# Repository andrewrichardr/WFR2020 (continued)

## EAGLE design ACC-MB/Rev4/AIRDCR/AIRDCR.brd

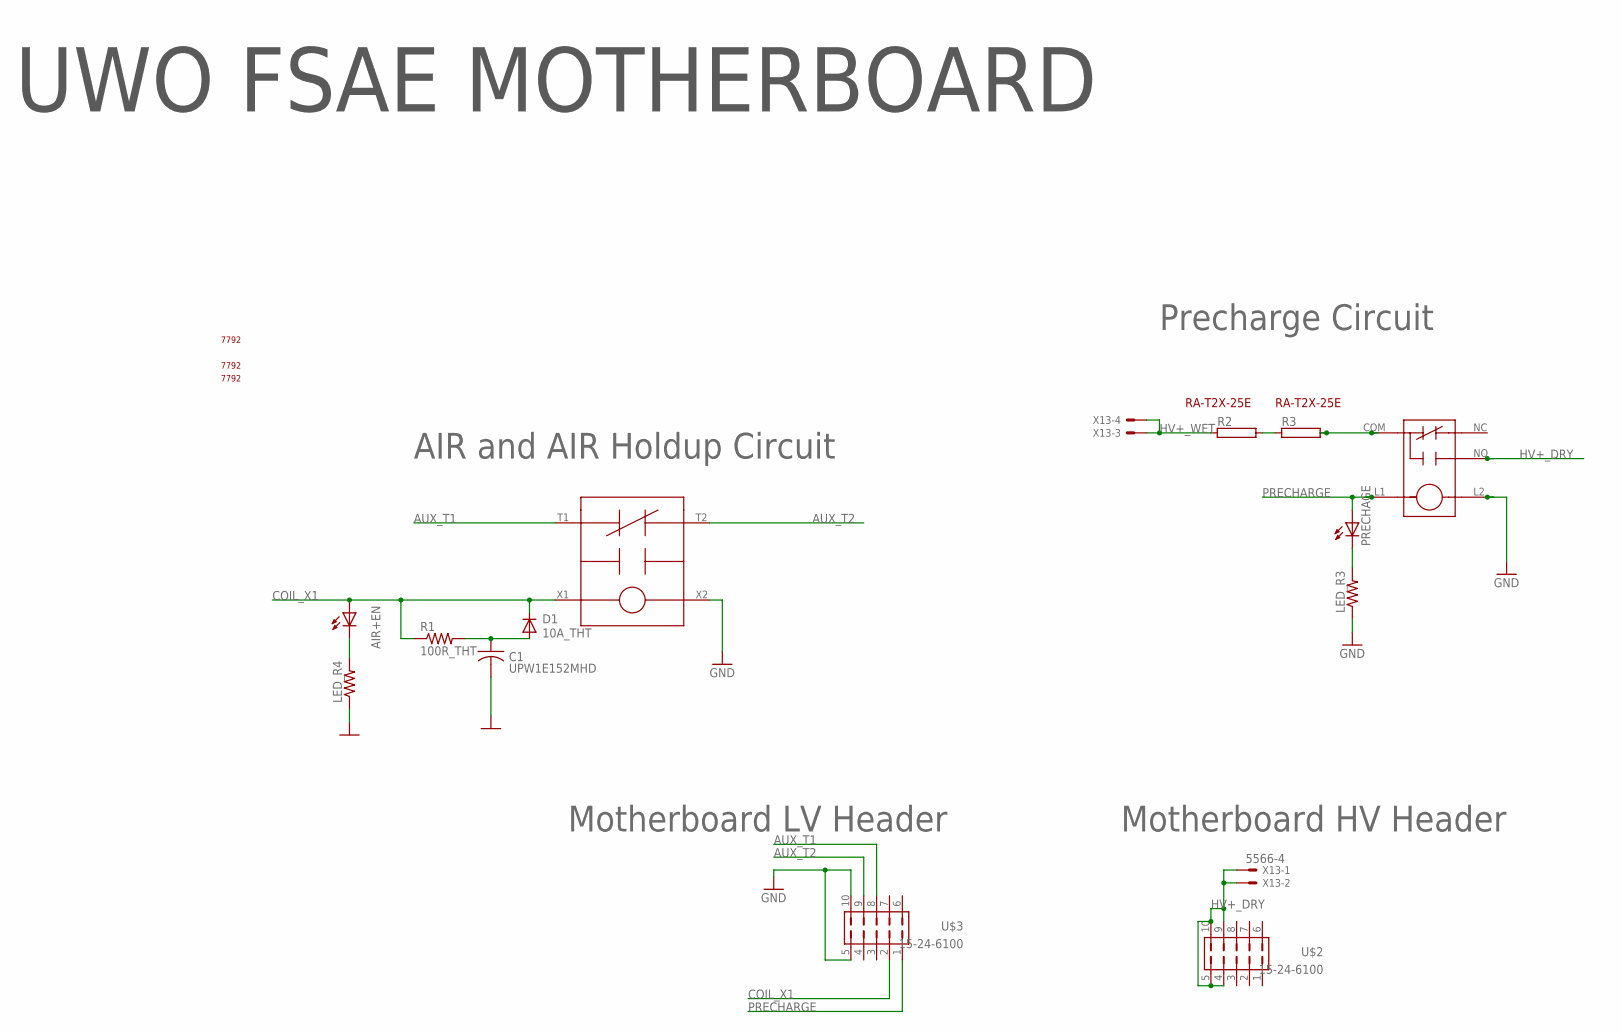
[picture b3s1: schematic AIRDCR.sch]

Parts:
AIR+EN: LEDCHIPLED_0805; CHIPLED_0805
C1: UPW1E152MHD; CAPPRD750W65D1800H3700B
D1: 10A_THT; DIOAD1570W120L850D500B
LED_R3, LED_R4: R-US_R0805; R0805
PRECHAGE: LEDCHIPLED_0805; CHIPLED_0805
R1: 100R_THT; RESAD976W63L650D250B
R2, R3: RMG100-V; TO-247-2V
U$1: GV245BPB; GV224
U$2, U$3: 15-24-6100
U$4: G81C335
U$5, U$6, U$7: 7792
U$8, U$9: RA-T2X-25E
X13: 5566-4

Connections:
AUX_T1: U$1.T1, U$3.8
AUX_T2: U$1.T2, U$3.9
COIL_X1: AIR+EN.A, D1.1 (C), R1.1, U$1.X1, U$3.2
GND: C1.2, LED_R3.1, LED_R4.1, U$1.X2, U$3.5, U$3.10, U$4.L2
HV+_DRY: U$2.4, U$2.5, U$2.9, U$2.10, U$4.NO, X13.1, X13.2
HV+_WET: R2.1, X13.3, X13.4
unnamed: LED_R3.2, PRECHAGE.C
unnamed: C1.1, D1.2 (A), R1.2
unnamed: R2.2, R3.1
unnamed: AIR+EN.C, LED_R4.2
unnamed: R3.2, U$4.COM
PRECHARGE: PRECHAGE.A, U$3.1, U$4.L1

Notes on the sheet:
UWO FSAE MOTHERBOARD
AIR and AIR Holdup Circuit
Precharge Circuit
Motherboard LV Header
Motherboard HV Header

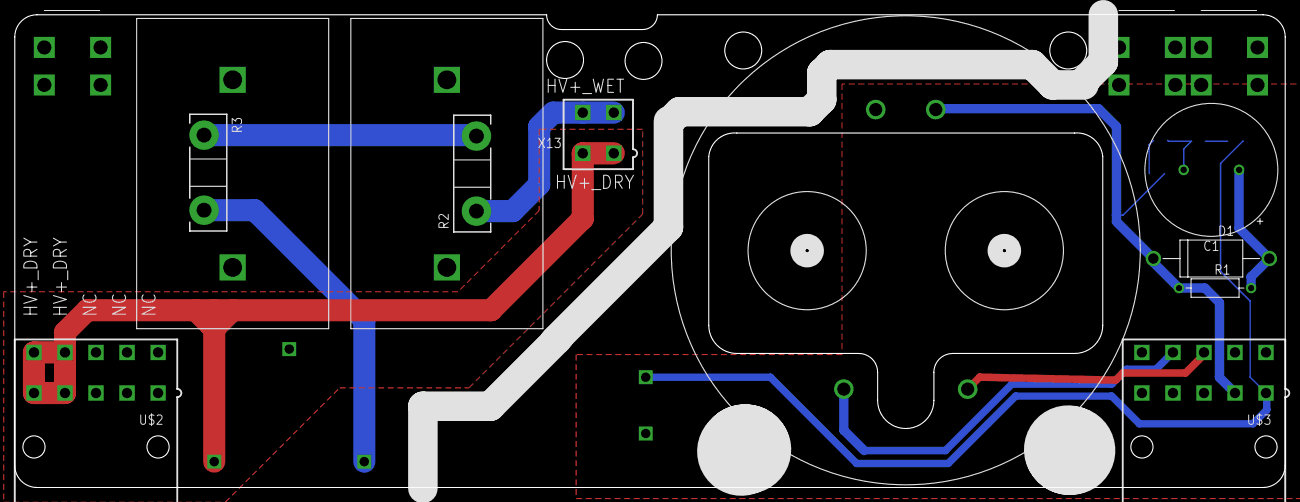
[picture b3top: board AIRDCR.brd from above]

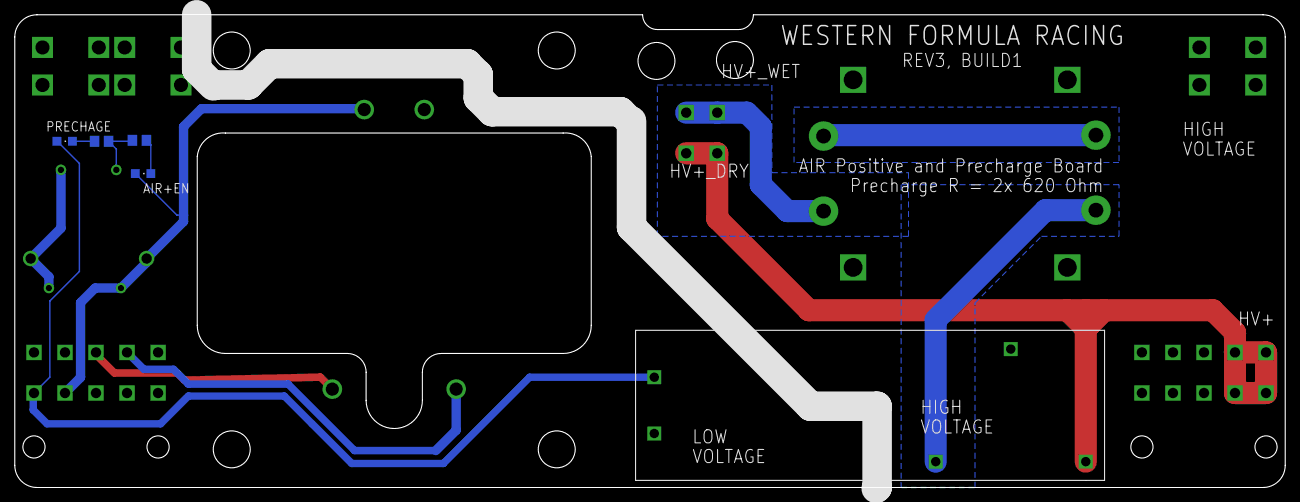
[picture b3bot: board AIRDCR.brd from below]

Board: 2 copper layers, 172.0 x 64.0 mm, 19 parts (5 on the bottom side), 12 nets.

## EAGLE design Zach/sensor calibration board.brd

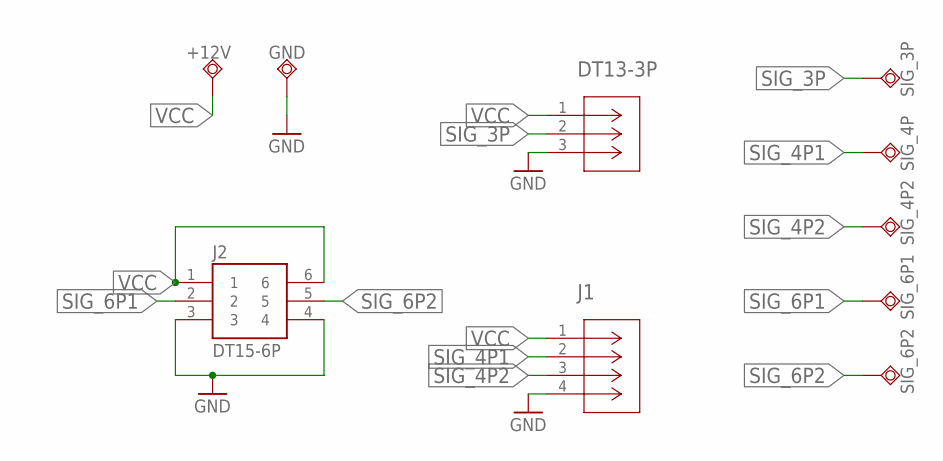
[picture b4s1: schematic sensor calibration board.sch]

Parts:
+12V: TPSQPAD1-20Y; P1-20Y
DT13-3P: DTF13-3P; CONN3_DTF13-3P
GND: TPSQPAD1-20Y; P1-20Y
J1: DT15-4P-G003S; CONN4_DT15-4P-G003
J2: DT15-6P; TE_DT15-6P
SIG_3P, SIG_4P, SIG_4P2, SIG_6P1, SIG_6P2: TPSQPAD1-20Y; P1-20Y

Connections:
GND: DT13-3P.3, GND.1, J1.4, J2.3, J2.4
SIG_3P: DT13-3P.2, SIG_3P.1
SIG_4P1: J1.2, SIG_4P.1
SIG_4P2: J1.3, SIG_4P2.1
SIG_6P1: J2.2, SIG_6P1.1
SIG_6P2: J2.5, SIG_6P2.1
VCC: +12V.1, DT13-3P.1, J1.1, J2.1, J2.6

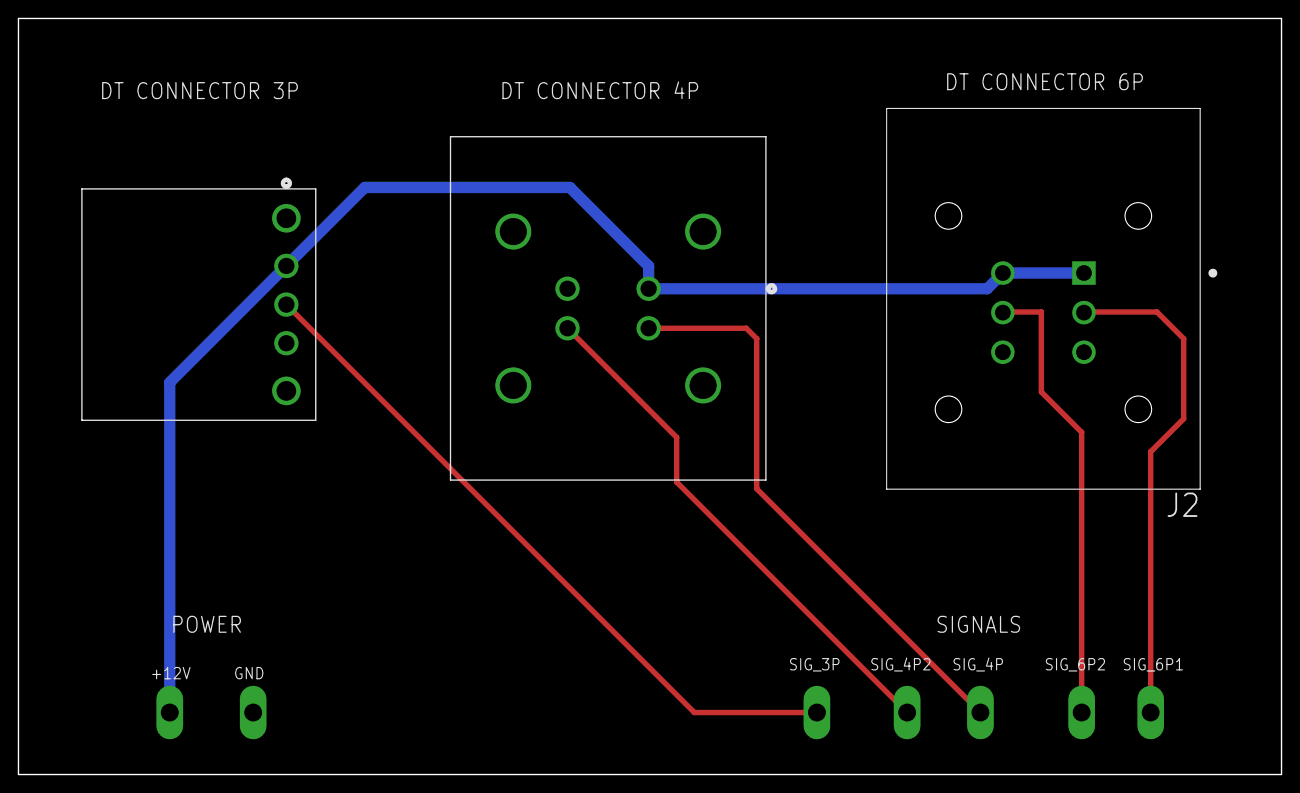
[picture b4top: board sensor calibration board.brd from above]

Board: 2 copper layers, 142.0 x 85.0 mm, 10 parts (0 on the bottom side), 7 nets.

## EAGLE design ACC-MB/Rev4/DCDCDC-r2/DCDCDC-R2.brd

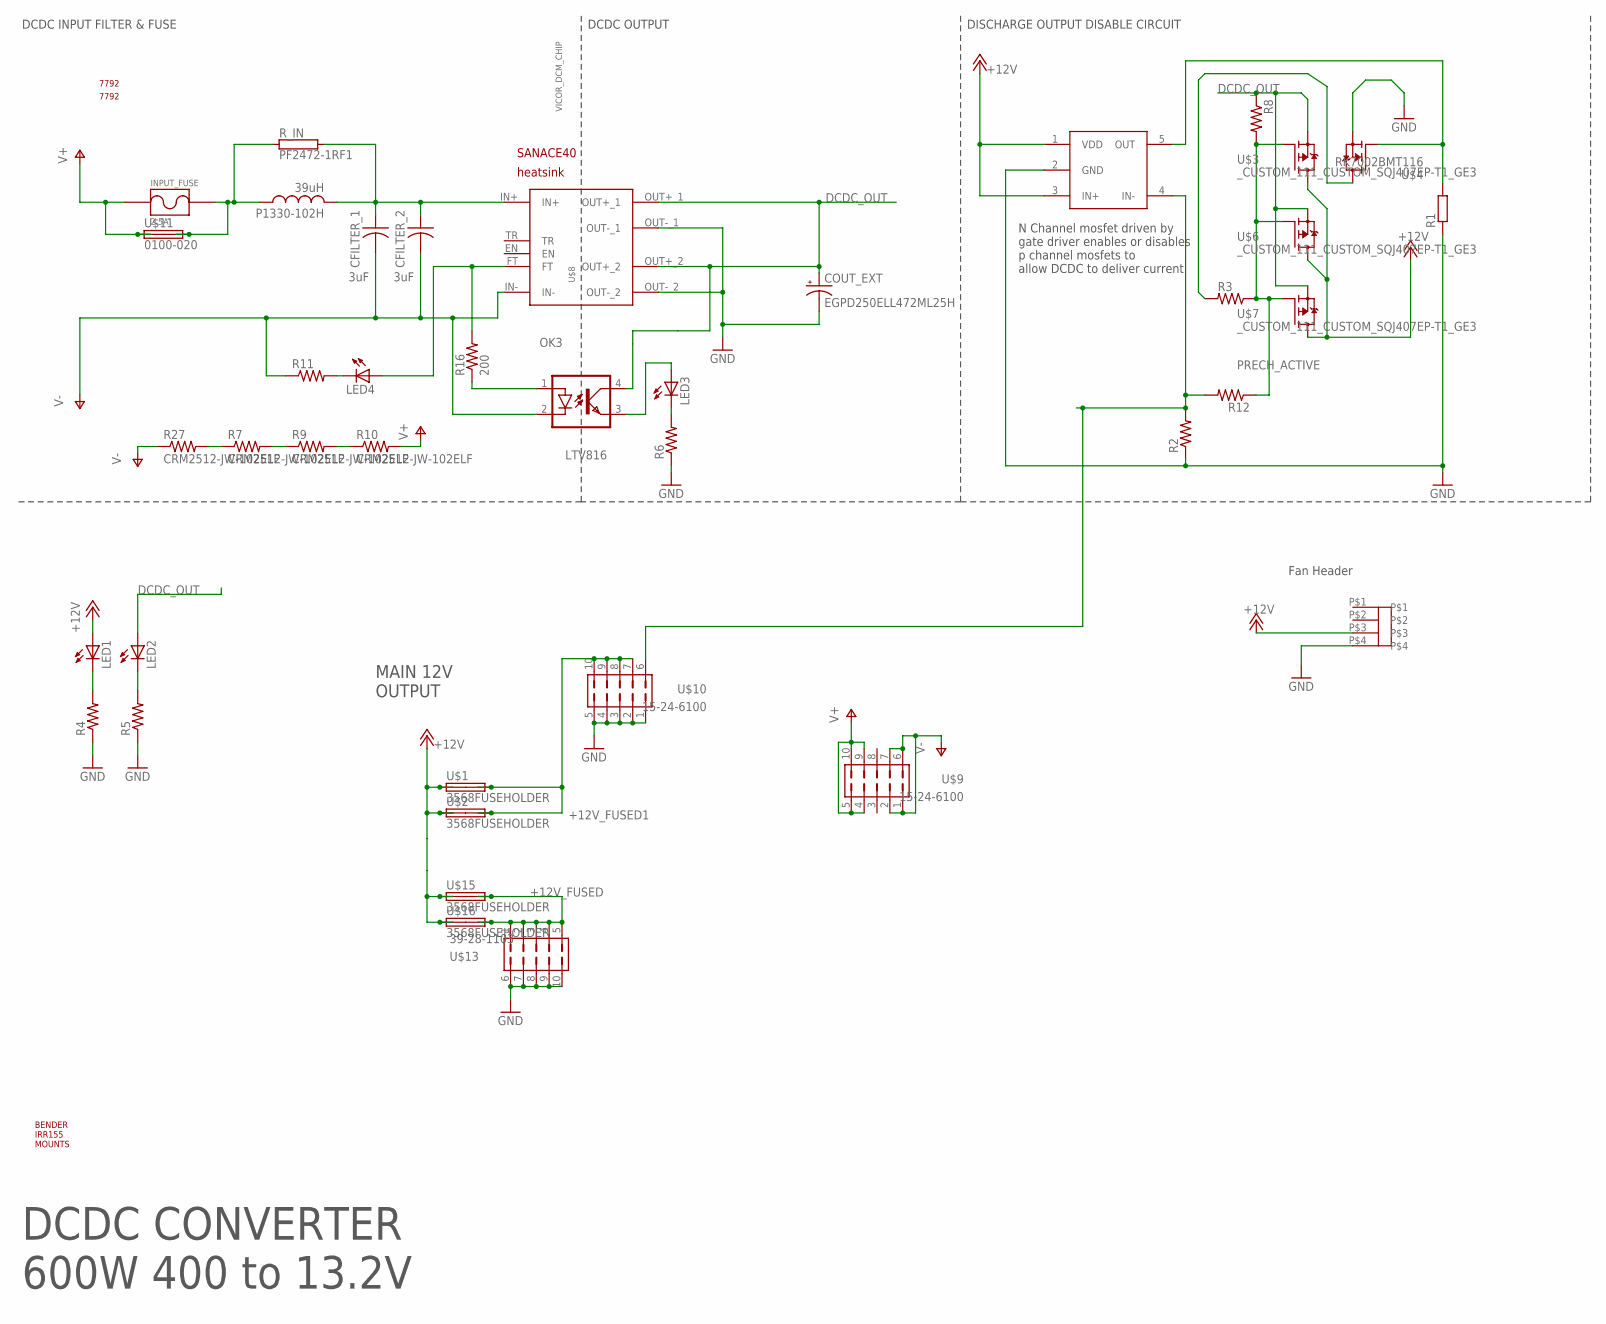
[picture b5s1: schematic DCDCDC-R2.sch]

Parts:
CFILTER_1, CFILTER_2: 3uF; CERALINK_FA3
COUT_EXT: EGPD250ELL472ML25H; E7,5-16
INPUT_FUSE: 2.5A; _CUSTOM_PARTS_LF_885
LED1, LED2, LED3, LED4: LEDCHIPLED_0805; CHIPLED_0805
OK3: LTV816; DIL04
P1330-102H: 39uH; L_1510_NONSTANDARD
R1: R-EU_R0805; R0805
R2, R3, R4, R5, R6, R8, R11, R12: R-US_R0805; R0805
R7, R9, R10, R27: CRM2512-JW-102ELF; R2512
R16: 200; R2010
R_IN: PF2472-1RF1; TO-247-2V
U$1, U$2, U$15, U$16: 3568FUSEHOLDER; 3568
U$3, U$6, U$7: _CUSTOM_111_CUSTOM_SQJ407EP-T1_GE3; _CUSTOM_111_CUSTOM_TRANS_SIRA90DP-T1-GE3
U$4: RK7002BMT116; SOT23
U$5: UCC27511AQDBVRQ1; SOT23-5L
U$8: VICOR_DCM_CHIP; VICOR_CHIP_HEATSINK
U$9, U$10: 15-24-6100
U$11: 0100-020
U$12: VICOR_HEATSINK_DOUBLE
U$13: 39-28-1103
U$14, U$17: 7792
U$18: 9GAX0412P3S0031; SANACE40
U$19: 470531000
U$20: BENDER_IRR155

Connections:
+12V: LED1.A, U$1.L1 (1A), U$1.L2 (1B), U$2.L1 (1A), U$2.L2 (1B), U$3.5 (D), U$5.1 (VDD), U$5.3 (IN+), U$6.5 (D), U$7.5 (D), U$15.L1 (1A), U$15.L2 (1B), U$16.L1 (1A), U$16.L2 (1B), U$19.P$3
+12V_FUSED: U$13.1, U$13.2, U$13.3, U$13.4, U$13.5, U$15.R1 (2A), U$15.R2 (2B), U$16.R1 (2A), U$16.R2 (2B)
+12V_FUSED1: U$1.R1 (2A), U$1.R2 (2B), U$2.R1 (2A), U$2.R2 (2B), U$10.7, U$10.8, U$10.9, U$10.10
DCDC_OUT: COUT_EXT.+, LED2.A, OK3.4 (COL), R8.1, U$3.1 (S), U$3.2 (S), U$3.3 (S), U$6.1 (S), U$6.2 (S), U$6.3 (S), U$7.1 (S), U$7.2 (S), U$7.3 (S), U$8.OUT+_1, U$8.OUT+_2
GND: COUT_EXT.-, R1.1, R2.1, R4.1, R5.1, R6.1, U$4.2 (S), U$5.2 (GND), U$8.OUT-_1, U$8.OUT-_2, U$10.1, U$10.2, U$10.3, U$10.4, U$10.5, U$13.6, U$13.7, U$13.8, U$13.9, U$13.10, U$19.P$4
unnamed: R3.1, R8.2, R12.1, U$3.4 (G), U$6.4 (G), U$7.4 (G)
unnamed: R1.2, U$4.1 (G), U$5.5 (OUT)
unnamed: CFILTER_1.P$1 (1), CFILTER_2.P$1 (1), P1330-102H.P$2 (2), R_IN.2, U$8.IN+
unnamed: R3.2, U$4.3 (D)
unnamed: LED1.C, R4.2
unnamed: LED2.C, R5.2
unnamed: LED4.A, R16.2, U$8.FT
unnamed: OK3.1 (A), R16.1
unnamed: LED3.C, R6.2
unnamed: LED3.A, OK3.3 (EMIT)
unnamed: LED4.C, R11.2
unnamed: R7.1, R27.2
unnamed: R7.2, R9.1
unnamed: R9.2, R10.1
PRECH_ACTIVE: R2.2, R12.2, U$5.4 (IN-), U$10.6
V+: INPUT_FUSE.P$1, R10.2, U$9.4, U$9.5, U$9.9, U$9.10, U$11.P$1 (1A), U$11.P$3 (1B)
V+_FUSED: INPUT_FUSE.P$2, P1330-102H.P$1 (1), R_IN.1, U$11.P$2 (2A), U$11.P$4 (2B)
V-: CFILTER_1.P$2 (2), CFILTER_2.P$2 (2), OK3.2 (C), R11.1, R27.1, U$8.IN-, U$9.1, U$9.2, U$9.6, U$9.7

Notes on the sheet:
DCDC CONVERTER 600W 400 to 13.2V
DISCHARGE OUTPUT DISABLE CIRCUIT
Fan Header
MAIN 12V OUTPUT
DCDC OUTPUT
DCDC INPUT FILTER & FUSE
N Channel mosfet driven by gate driver enables or disables p channel mosfets to allow DCDC to deliver current

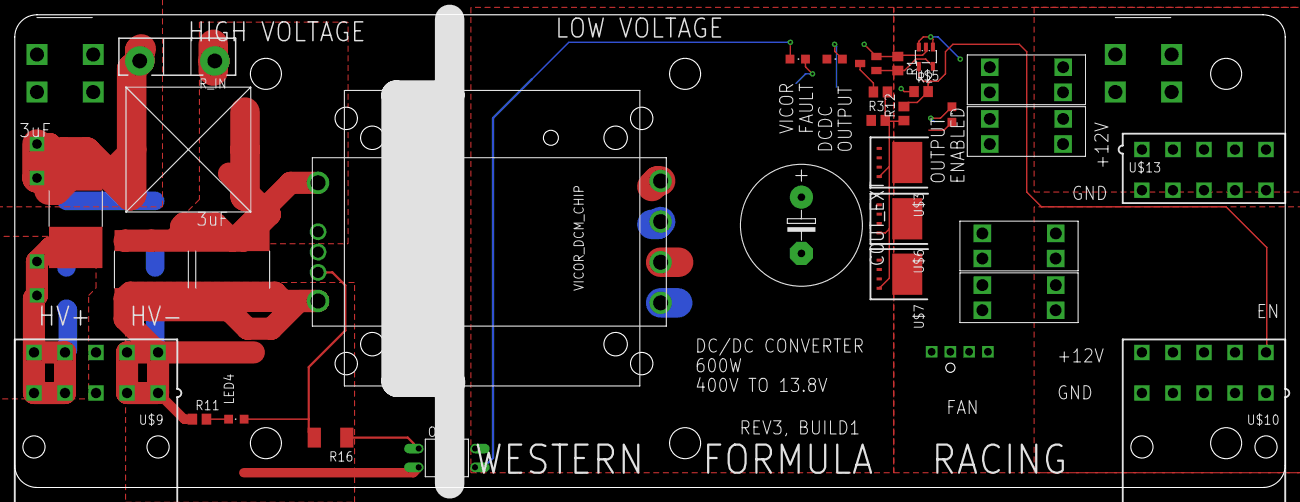
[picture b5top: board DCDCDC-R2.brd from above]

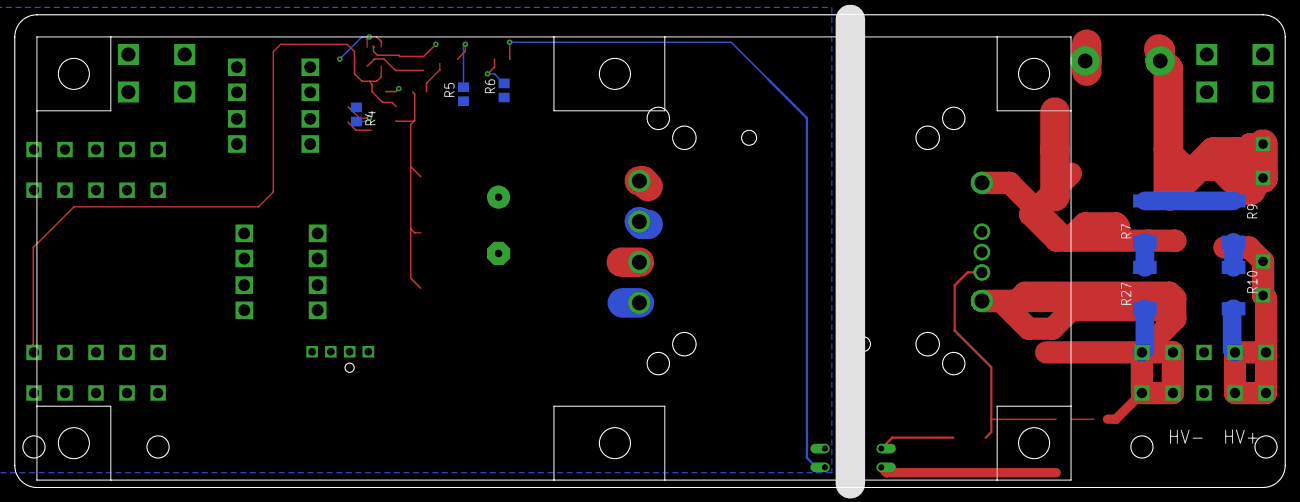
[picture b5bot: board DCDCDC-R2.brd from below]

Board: 2 copper layers, 172.0 x 64.0 mm, 45 parts (8 on the bottom side), 23 nets.

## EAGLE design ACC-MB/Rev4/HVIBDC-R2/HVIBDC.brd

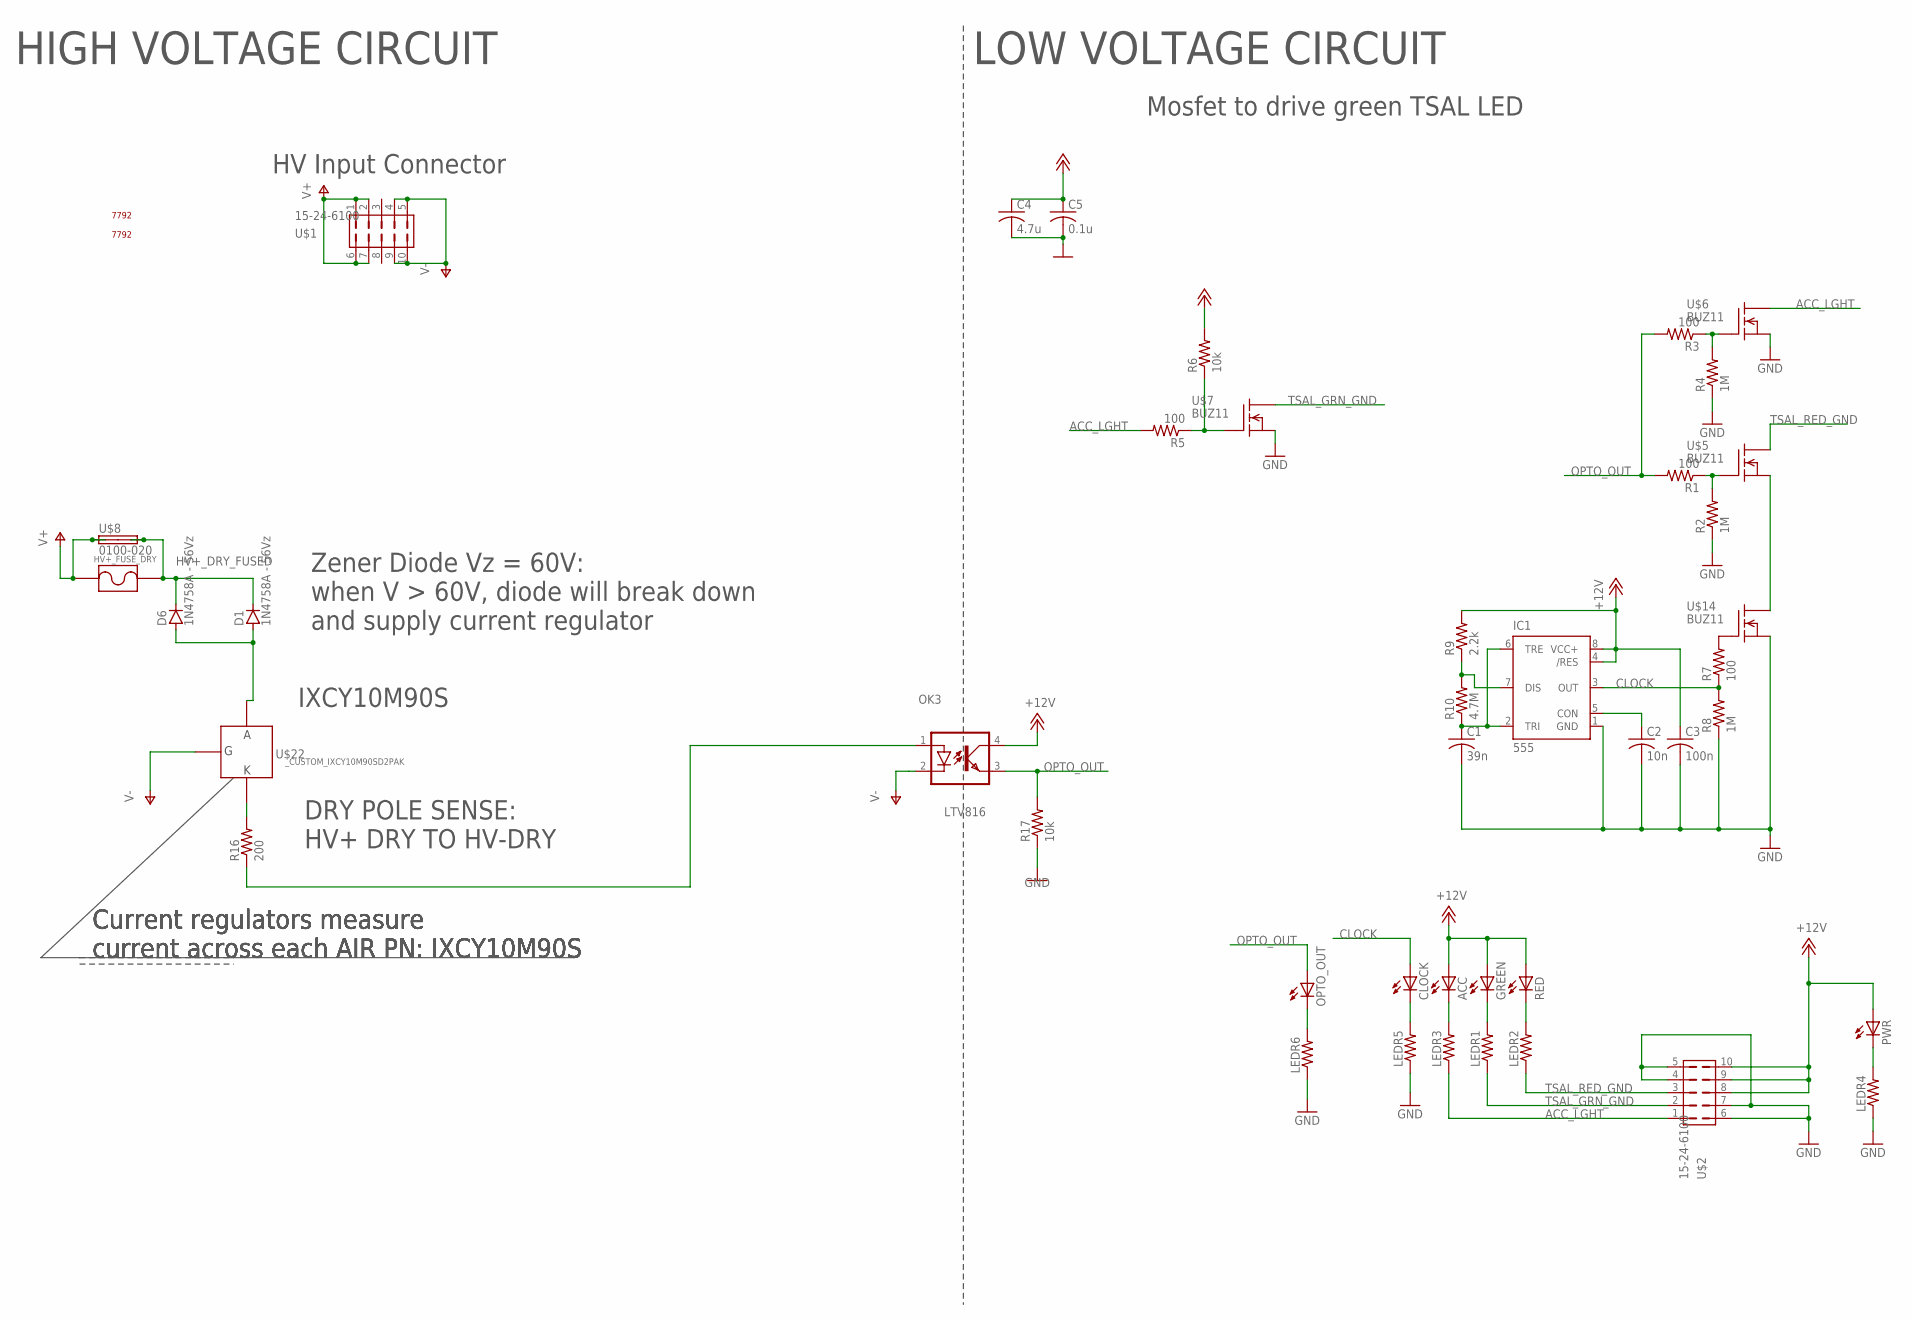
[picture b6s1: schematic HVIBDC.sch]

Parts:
ACC: LEDCHIPLED_0805; CHIPLED_0805
C1: 39n; C0805
C2: 10n; C0805
C3: 100n; C0805
C4: 4.7u; C0805
C5: 0.1u; C0805
CLOCK: LEDCHIPLED_0805; CHIPLED_0805
D1, D6: 1N4758A - 56Vz; DO201-15
GREEN: LEDCHIPLED_0805; CHIPLED_0805
HV+_FUSE_DRY: _CUSTOM_PARTS_LF_885
IC1: 555; DIP08
LEDR1, LEDR2, LEDR3, LEDR4, LEDR5, LEDR6: R-US_R0805; R0805
OK3: LTV816; DIL04
OPTO_OUT: LEDCHIPLED_0805; CHIPLED_0805
PWR: LEDCHIPLED_0805; CHIPLED_0805
R1, R3, R5, R7: 100; R0805
R2, R4, R8: 1M; R0805
R6, R17: 10k; R0805
R9: 2.2k; R0805
R10: 4.7M; R0805
R16: 200; R2010
RED: LEDCHIPLED_0805; CHIPLED_0805
U$1, U$2: 15-24-6100
U$3, U$4: 7792
U$5, U$6, U$7, U$14: BUZ11; TO220
U$8: 0100-020
U$22: _CUSTOM_IXCY10M90SD2PAK; TO228P991X238-3

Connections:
+12V: ACC.A, C3.1, C4.1, C5.1, GREEN.A, IC1.4 (/RES), IC1.8 (VCC+), OK3.4 (COL), PWR.A, R6.2, R9.2, RED.A, U$2.8, U$2.9, U$2.10
ACC_LGHT: LEDR3.1, R5.2, U$2.1, U$6.2 (D)
CLOCK: CLOCK.A, IC1.3 (OUT), R7.1, R8.2
GND: C1.2, C2.2, C3.2, C4.2, C5.2, IC1.1 (GND), LEDR4.1, LEDR5.1, LEDR6.1, R2.1, R4.1, R8.1, R17.1, U$2.4, U$2.5, U$2.6, U$2.7, U$6.3 (S), U$7.3 (S), U$14.3 (S)
HV+_DRY_FUSED: D1.C, D6.C, HV+_FUSE_DRY.P$1, U$8.P$2 (2A), U$8.P$4 (2B)
unnamed: R1.1, R2.2, U$5.1 (G)
unnamed: R3.1, R4.2, U$6.1 (G)
unnamed: R5.1, R6.1, U$7.1 (G)
unnamed: C2.1, IC1.5 (CON)
unnamed: IC1.7 (DIS), R9.1, R10.2
unnamed: CLOCK.C, LEDR5.2
unnamed: R7.2, U$14.1 (G)
unnamed: LEDR6.2, OPTO_OUT.C
unnamed: C1.1, IC1.2 (TRI), IC1.6 (TRE), R10.1
unnamed: ACC.C, LEDR3.2
unnamed: GREEN.C, LEDR1.2
unnamed: U$5.3 (S), U$14.2 (D)
unnamed: LEDR2.2, RED.C
unnamed: LEDR4.2, PWR.C
unnamed: R16.2, U$22.2 (K)
unnamed: D1.A, D6.A, U$22.3 (A)
unnamed: OK3.1 (A), R16.1
OPTO_OUT: OK3.3 (EMIT), OPTO_OUT.A, R1.2, R3.2, R17.2
TSAL_GRN_GND: LEDR1.1, U$2.2, U$7.2 (D)
TSAL_RED_GND: LEDR2.1, U$2.3, U$5.2 (D)
V+: HV+_FUSE_DRY.P$2, U$1.1, U$1.2, U$1.6, U$1.7, U$8.P$1 (1A), U$8.P$3 (1B)
V-: OK3.2 (C), U$1.4, U$1.5, U$1.9, U$1.10, U$22.1 (G)

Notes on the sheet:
HIGH VOLTAGE CIRCUIT
LOW VOLTAGE CIRCUIT
Mosfet to drive green TSAL LED
Current regulators measure current across each AIR PN: IXCY10M90S
DRY POLE SENSE: HV+ DRY TO HV-DRY
IXCY10M90S
Zener Diode Vz = 60V: when V > 60V, diode will break down and supply current regulator
HV Input Connector

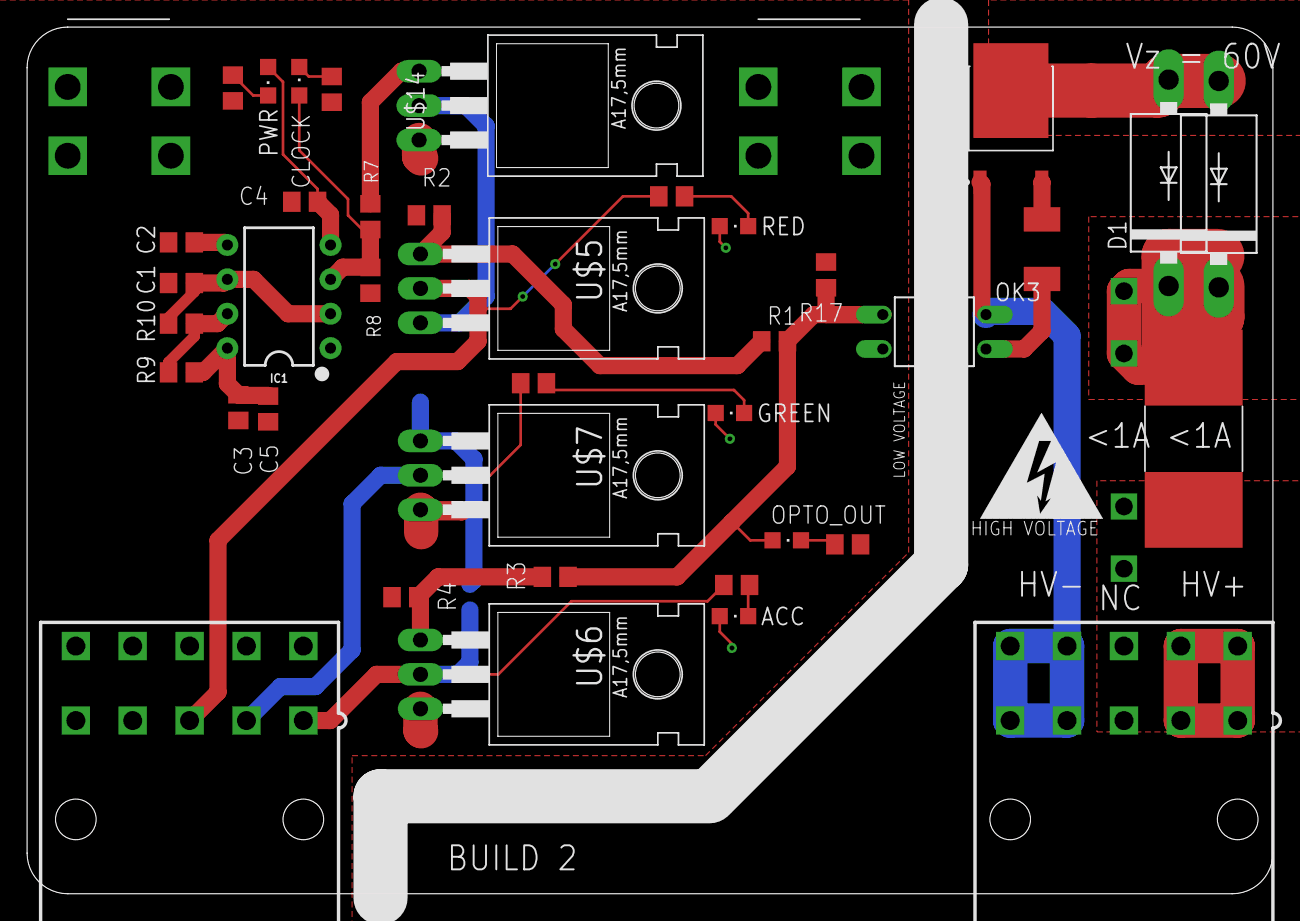
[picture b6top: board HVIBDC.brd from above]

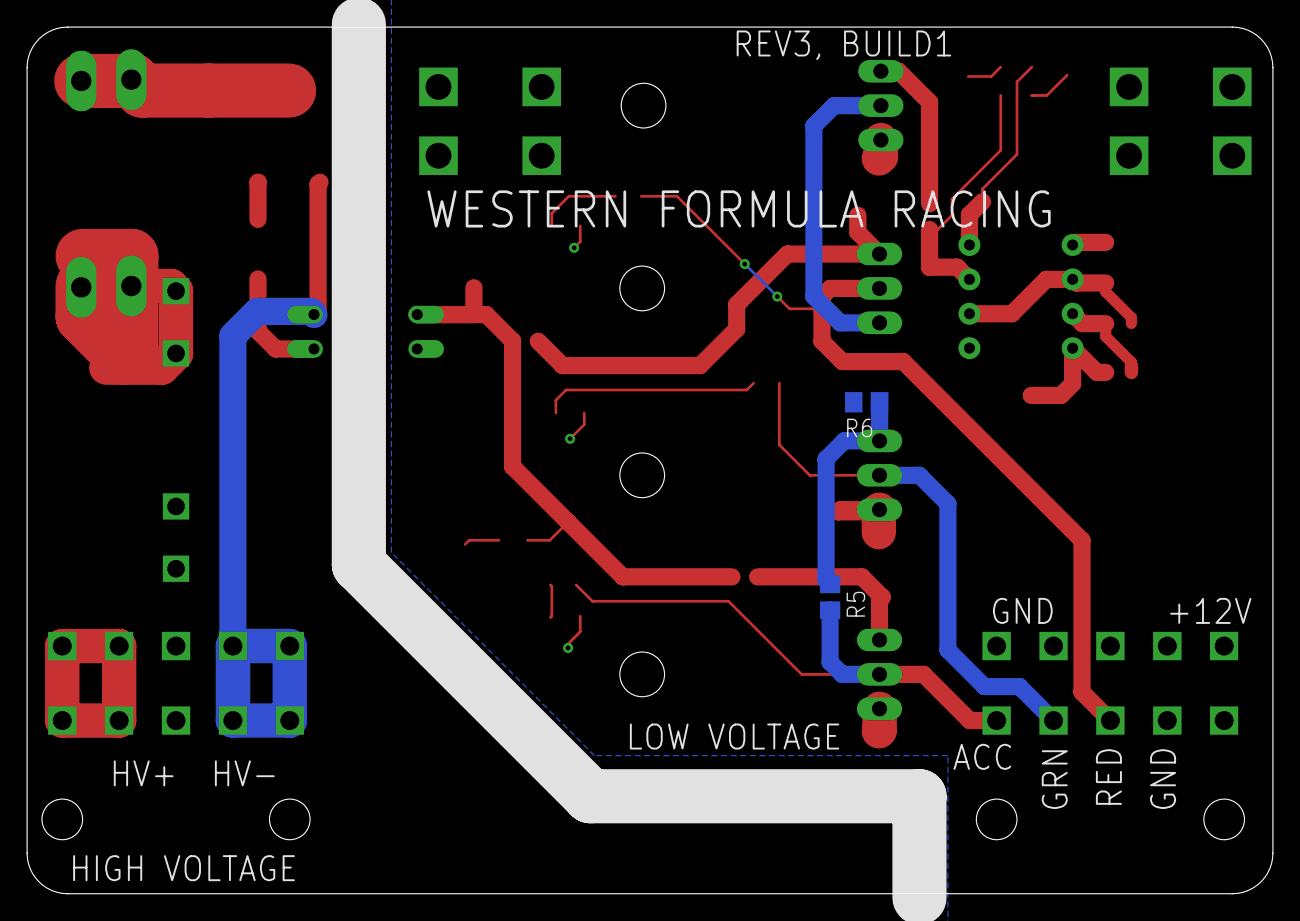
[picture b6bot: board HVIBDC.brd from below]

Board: 2 copper layers, 92.0 x 64.0 mm, 44 parts (2 on the bottom side), 27 nets.

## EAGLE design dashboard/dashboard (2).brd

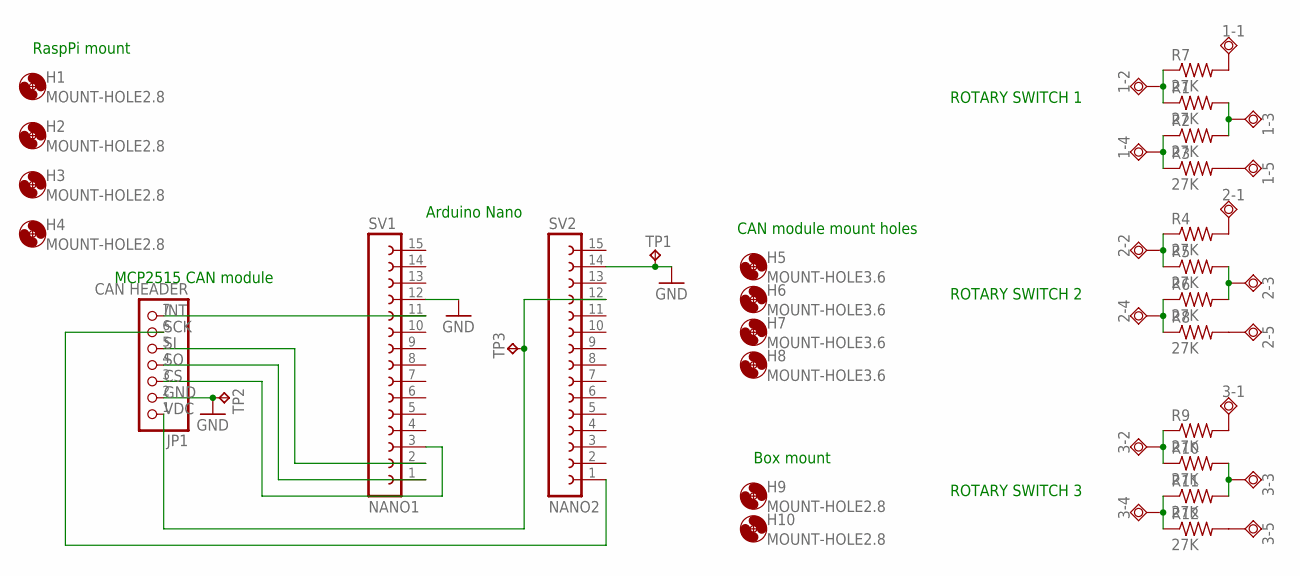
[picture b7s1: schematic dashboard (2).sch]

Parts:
1-1, 1-5, 2-1, 2-5, 3-1, 3-5: TPSQPAD1-13Y; P1-13Y
1-2, 1-3, 1-4, 2-2, 2-3, 2-4, 3-2, 3-3, 3-4: TPSQPAD1-13; P1-13
H1, H2, H3, H4, H9, H10: MOUNT-HOLE2.8; 2,8
H5, H6, H7, H8: MOUNT-HOLE3.6; 3,6
JP1: CAN HEADER; 1X07M
R1, R2, R3, R4, R5, R6, R7, R8, R9, R10, R11, R12: 27K; 0309/10
SV1: NANO1; FE15
SV2: NANO2; FE15
TP1, TP2, TP3: TPTP20SQ; TP20SQ

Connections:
2-2: 2-2.1, R4.1, R5.1
CS: JP1.3, SV1.3
GND: JP1.2, SV1.12, SV2.14, TP1.TP, TP2.TP
INT: JP1.7, SV1.11
unnamed: 1-1.1, R7.2
unnamed: 1-4.1, R2.1, R3.1
unnamed: 2-3.1, R5.2, R6.2
unnamed: 2-1.1, R4.2
unnamed: 3-1.1, R9.2
unnamed: 1-2.1, R1.1, R7.1
unnamed: 1-3.1, R1.2, R2.2
unnamed: 2-4.1, R6.1, R8.1
unnamed: 3-2.1, R9.1, R10.1
unnamed: 3-3.1, R10.2, R11.2
unnamed: 3-4.1, R11.1, R12.1
unnamed: 2-5.1, R8.2
unnamed: 1-5.1, R3.2
unnamed: 3-5.1, R12.2
SCK: JP1.6, SV2.1
SI: JP1.5, SV1.2
SO: JP1.4, SV1.1
VDC: JP1.1, SV2.12, TP3.TP

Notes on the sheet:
CAN module mount holes
Box mount
RaspPi mount
MCP2515 CAN module
Arduino Nano
ROTARY SWITCH 1
ROTARY SWITCH 2
ROTARY SWITCH 3

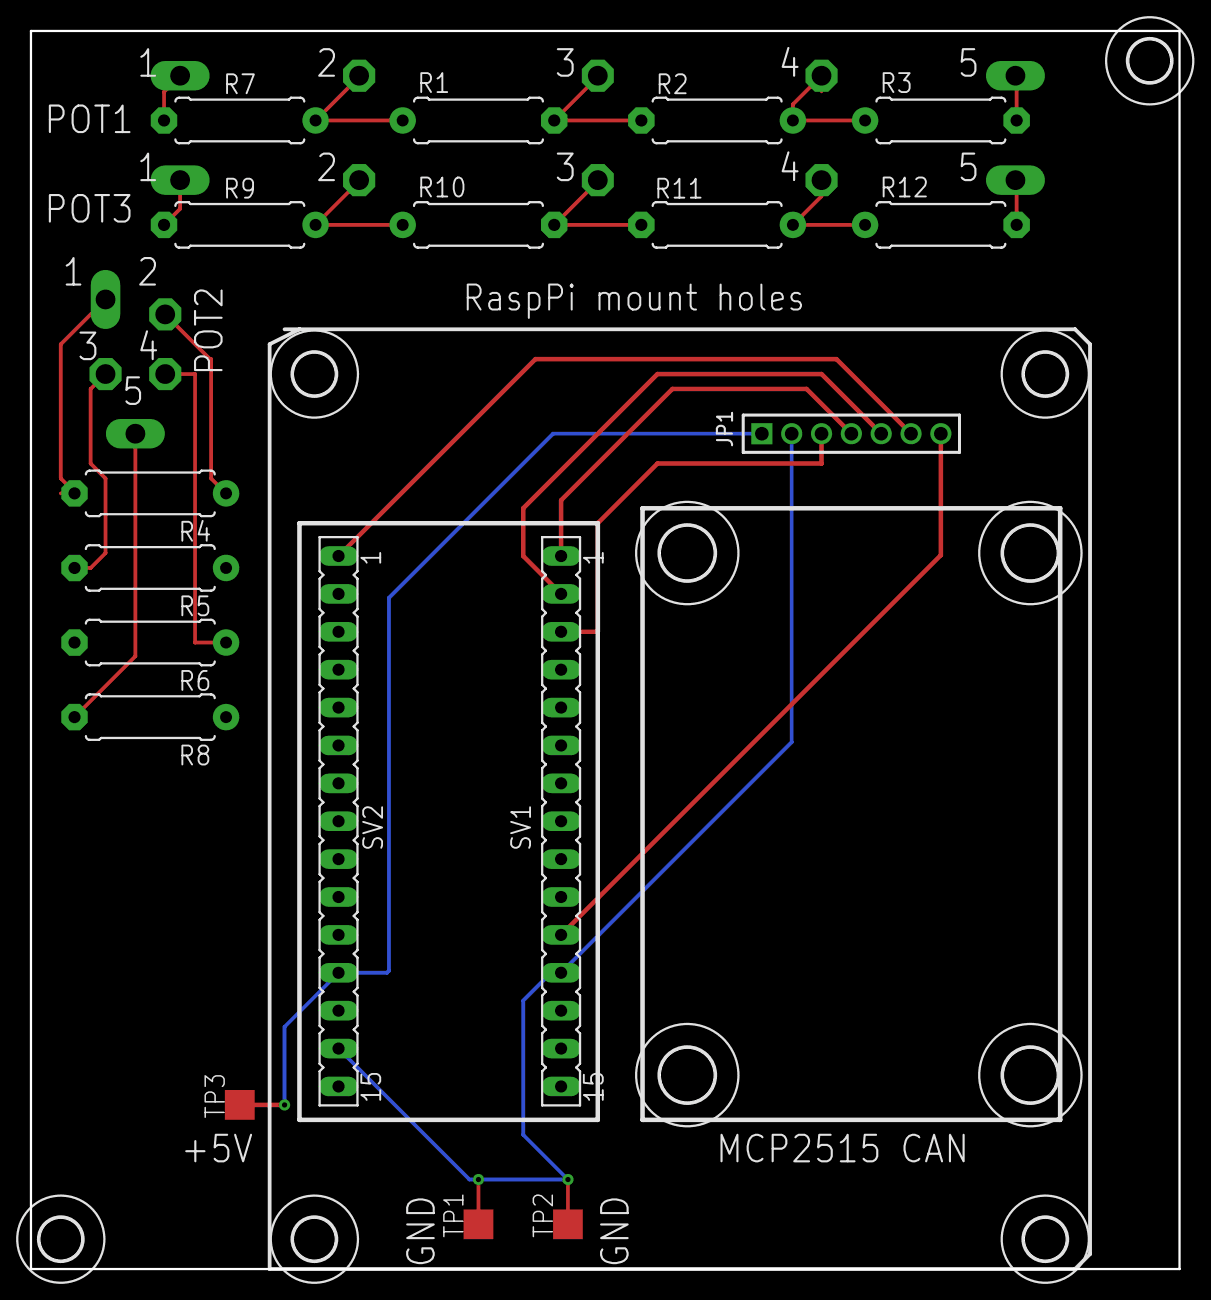
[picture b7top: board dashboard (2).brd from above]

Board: 2 copper layers, 77.0 x 83.0 mm, 43 parts (0 on the bottom side), 22 nets.

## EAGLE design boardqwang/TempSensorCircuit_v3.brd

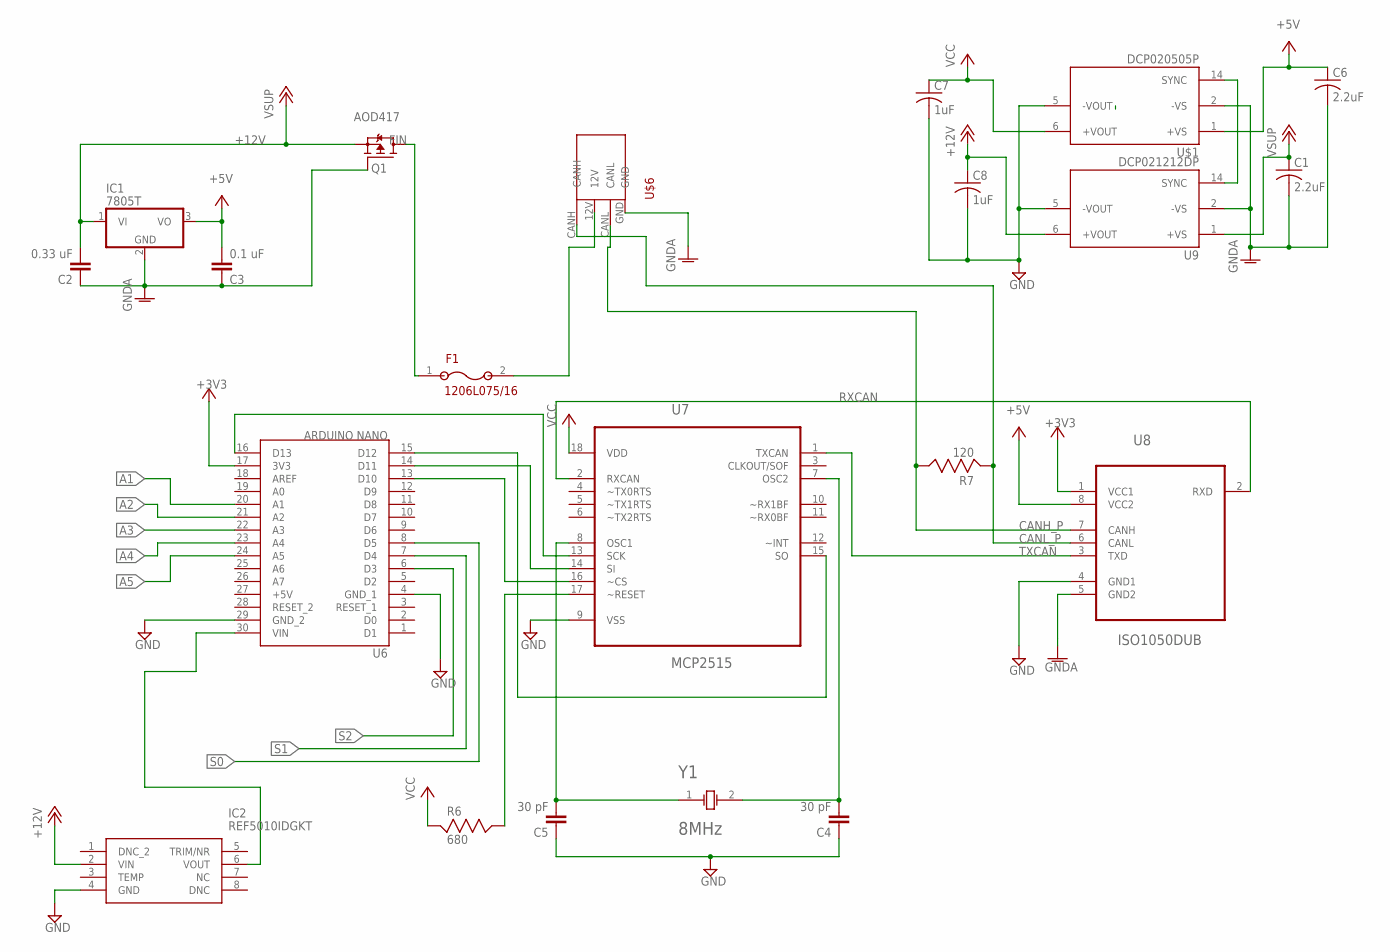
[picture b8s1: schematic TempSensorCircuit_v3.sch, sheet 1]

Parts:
C1, C6: 2.2uF; C0805
C2: 0.33 uF; C5B2.5
C3: 0.1 uF; C5B2.5
C4, C5: 30 pF; C5B2.5
C7, C8: 1uF; C0805
F1: 1206L075/16
IC1: 7805T; TO220H
IC2: REF5010IDGKT; SOP65P490X110-8N
Q1: AOD417; TO252
R6: 680; RESC2012X60
R7: 120; RESC2012X60
U6: ARDUINO NANO; NANO
U7: MCP2515; DIP254P762X432-18
U8: ISO1050DUB; SOP254P1040X485-8N
U9: DCP021212DP; DIP763W46P254L1969H533Q14
U$1: DCP020505P; DIP763W46P254L1969H533Q14
U$6: 0026013142-ND
Y1: 8MHz; XTAL_HC49P488W43L1135T465H360

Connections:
+3V3: U6.17 (3V3), U8.1 (VCC1)
+5V: C3.2, C6.1, IC1.3 (VO), U6.27 (+5V), U8.8 (VCC2), U$1.1 (+VS)
+12V: C1.1, C2.2, C8.1, IC1.1 (VI), IC2.2 (VIN), Q1.2 (S), U9.1 (+VS), U9.6 (+VOUT)
A1: U6.20 (A1); also elsewhere on the board
A2: U6.21 (A2); also elsewhere on the board
A3: U6.22 (A3); also elsewhere on the board
A4: U6.23 (A4); also elsewhere on the board
A5: U6.24 (A5); also elsewhere on the board
CANH_P: R7.2, U8.7 (CANH), U$6.CANL
CANL_P: R7.1, U8.6 (CANL), U$6.CANH
FIN: F1.1, Q1.3 (D)
GND: C4.1, C5.1, C7.2, C8.2, IC2.4 (GND), U6.4 (GND_1), U6.29 (GND_2), U7.9 (VSS), U8.4 (GND1), U9.5 (-VOUT), U$1.5 (-VOUT); also elsewhere on the board
GNDA: C1.2, C2.1, C3.1, C6.2, IC1.2 (GND), Q1.1 (G), U8.5 (GND2), U9.2 (-VS), U$1.2 (-VS), U$6.GND
unnamed: R6.2, U7.17 (~RESET)
unnamed: U6.16 (D13), U7.13 (SCK)
unnamed: U6.14 (D11), U7.14 (SI)
unnamed: U6.15 (D12), U7.15 (SO)
unnamed: U6.13 (D10), U7.16 (~CS)
unnamed: IC2.6 (VOUT), U6.30 (VIN)
unnamed: F1.2, U$6.12V
unnamed: U9.14 (SYNC), U$1.14 (SYNC)
OSC_N: C5.2, U7.8 (OSC1), Y1.1
OSC_P: C4.2, U7.7 (OSC2), Y1.2
RXCAN: U7.2 (RXCAN), U8.2 (RXD)
S0: U6.8 (D5); also elsewhere on the board
S1: U6.7 (D4); also elsewhere on the board
S2: U6.6 (D3); also elsewhere on the board
TXCAN: U7.1 (TXCAN), U8.3 (TXD)
VCC: C7.1, R6.1, U7.18 (VDD), U$1.6 (+VOUT); also elsewhere on the board
